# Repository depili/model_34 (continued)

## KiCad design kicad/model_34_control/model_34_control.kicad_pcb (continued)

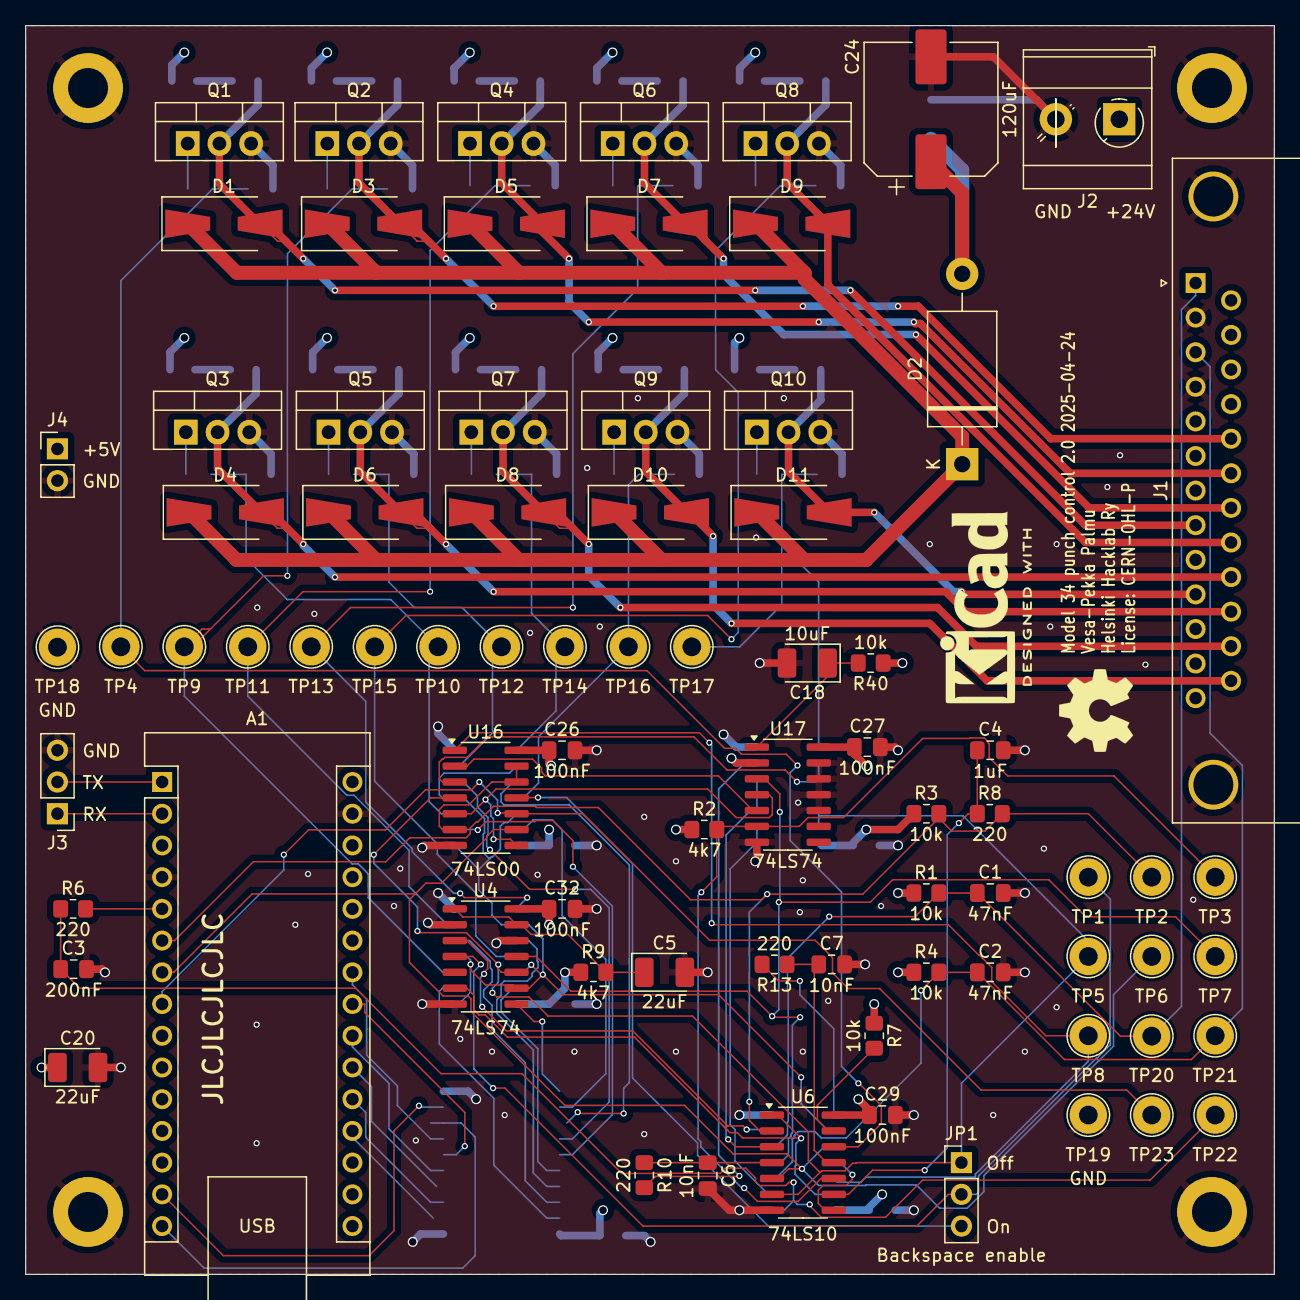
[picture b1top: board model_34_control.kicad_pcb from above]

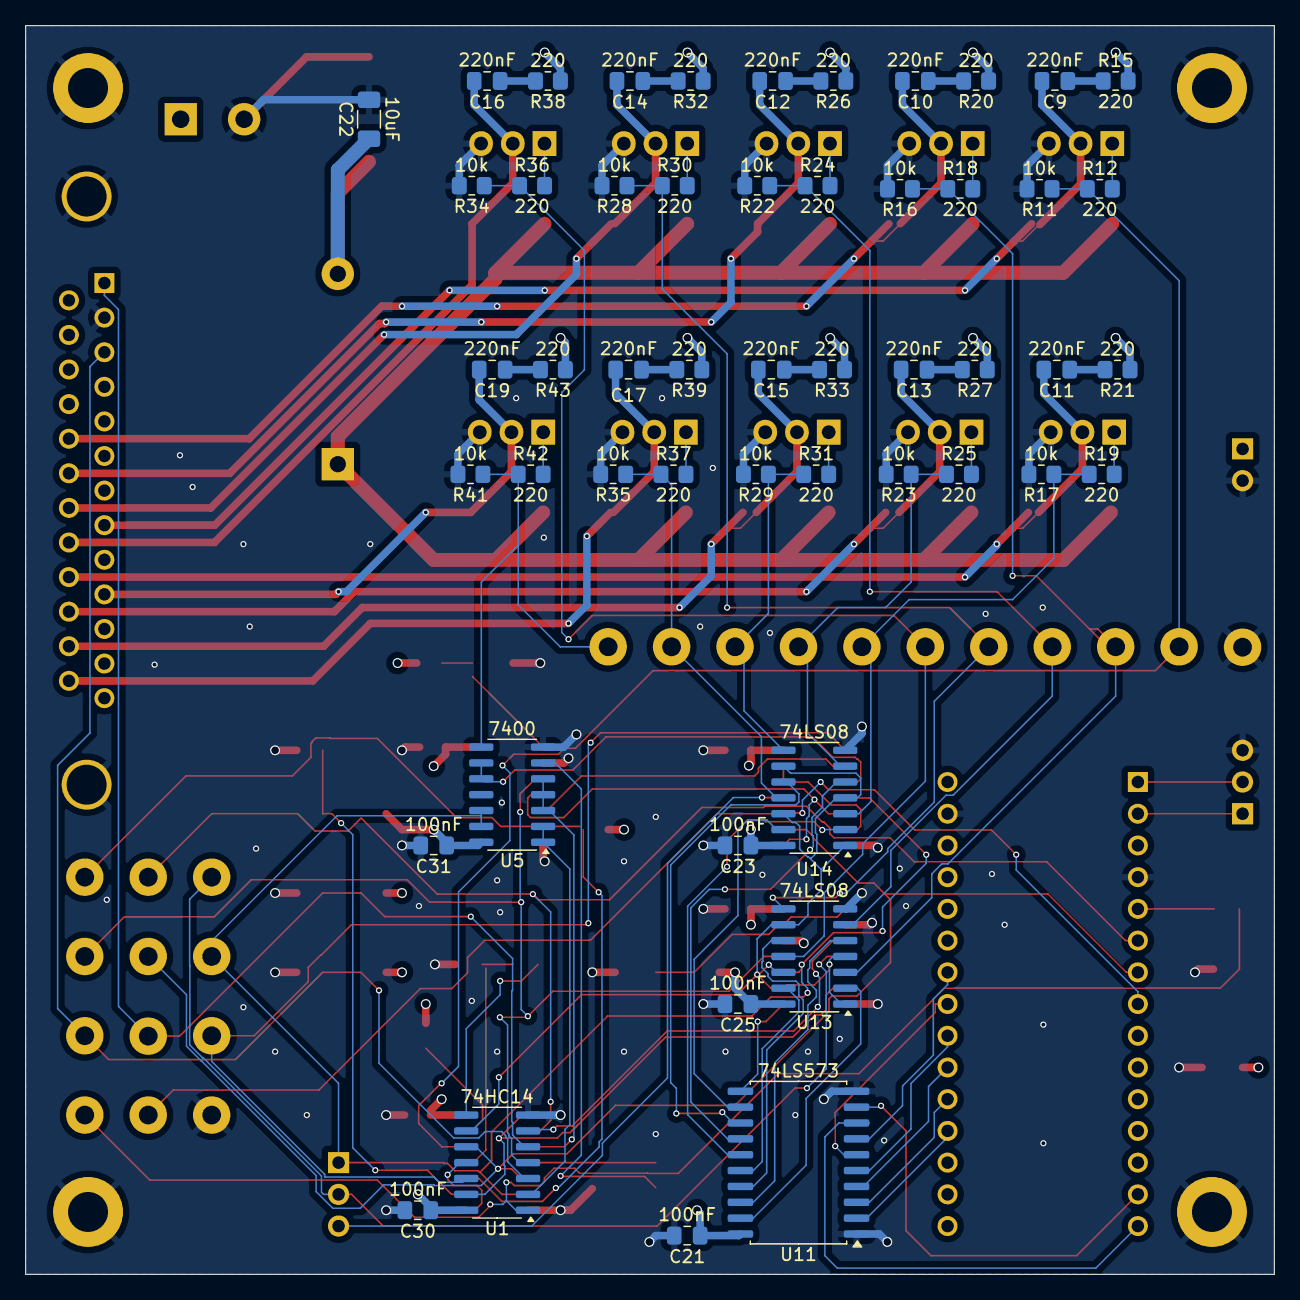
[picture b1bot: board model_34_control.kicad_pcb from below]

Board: 4 copper layers, 100.0 x 100.0 mm, 136 parts (51 on the bottom side), 94 nets.

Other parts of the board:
H1, H2, H3, H4: MountingHole_Pad; MountingHole_3.2mm_M3_DIN965_Pad
LOGO1: KiCad-Logo2_6mm_SilkScreen
LOGO2: OSHW-Symbol_6.7x6mm_SilkScreen

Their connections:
GND: H1.1, H2.1, H3.1, H4.1; also elsewhere on the board

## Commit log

2025-05-04 Initial commit of the first working hardware revision.
2025-05-05 Add gitignore
